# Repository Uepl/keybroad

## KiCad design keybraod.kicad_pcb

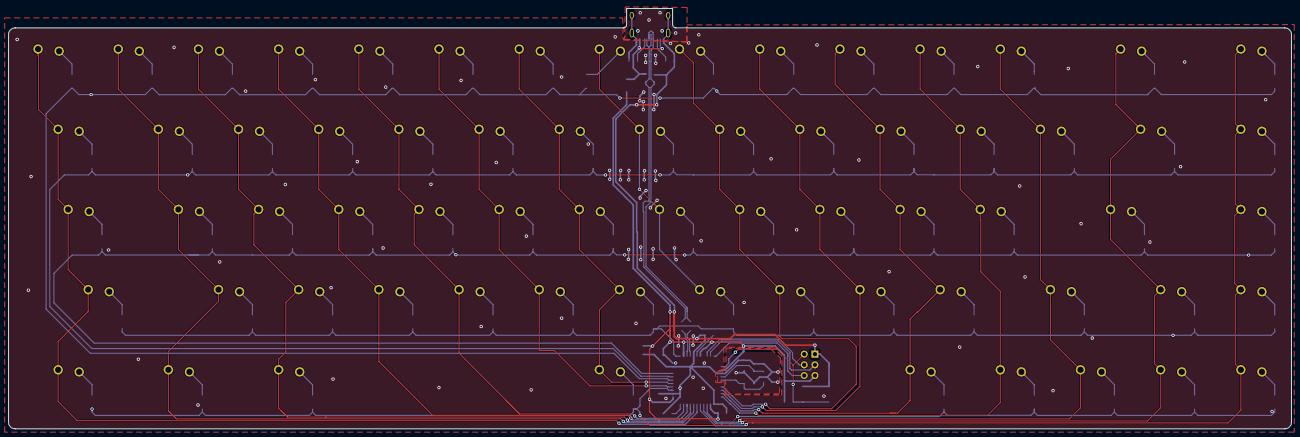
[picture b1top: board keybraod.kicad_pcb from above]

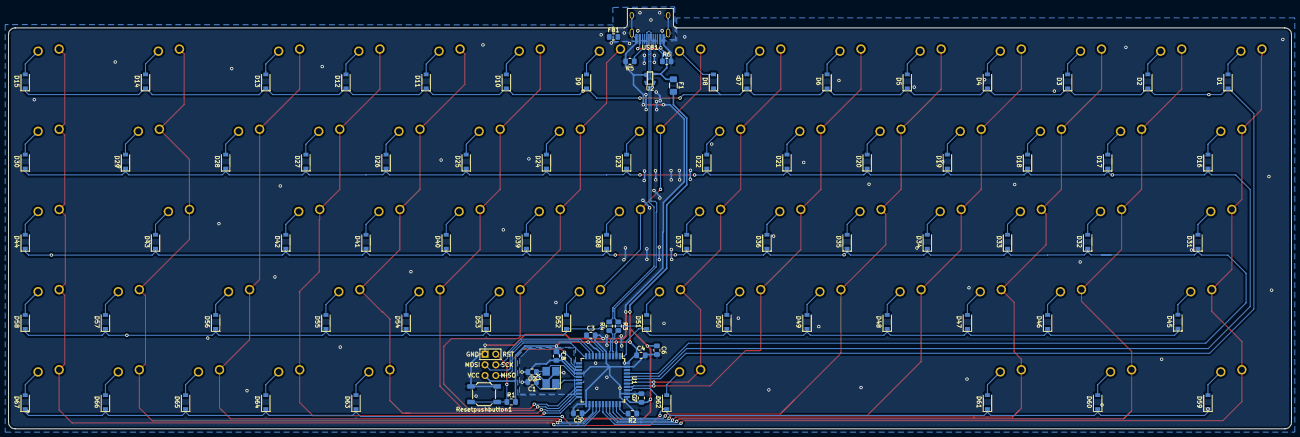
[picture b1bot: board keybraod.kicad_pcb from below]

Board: 2 copper layers, 304.8 x 99.9 mm, 156 parts (156 on the bottom side), 86 nets.

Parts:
C1, C2: 22p; C_0805_2012Metric_Pad1.15x1.40mm_HandSolder
C3: C_Small; C_0805_2012Metric_Pad1.15x1.40mm_HandSolder
C4, C5, C6, C7: 0.1u; C_0805_2012Metric_Pad1.15x1.40mm_HandSolder
C8: 10u; C_0805_2012Metric_Pad1.15x1.40mm_HandSolder
D1, D2, D3, D4, D5, D6, D7, D8, D9, D10, D11, D12, D13, D14, D15, D16, D17, D18, D19, D20, D21, D22, D23, D24, D25, D26, D27, D28, D29, D30, D31, D32, D33, D34, D35, D36, D37, D38, D39, D40, D41, D42, D43, D44, D45, D46, D47, D48, D49, D50, D51, D52, D53, D54, D55, D56, D57, D58, D59, D60, D61, D62, D63, D64, D65, D66, D67: D; D_SOD-123
F1: 500m; Fuse_1206_3216Metric_Pad1.42x1.75mm_HandSolder
FB1: 60@100MHz; L_0805_2012Metric_Pad1.15x1.40mm_HandSolder
J1: AVR-ISP-6; Reset_Pretty-Mask
R1, R2: 10k; R_0805_2012Metric_Pad1.15x1.40mm_HandSolder
R3, R4: 22; R_0805_2012Metric_Pad1.15x1.40mm_HandSolder
R5, R6: 5.1k; R_0805_2012Metric_Pad1.15x1.40mm_HandSolder
Resetpushbutton1: SW_SKQG; SW_SPST_SKQG_WithStem
SW1: GRV; ALPS-1U
SW2: #1; ALPS-1U
SW3: #2; ALPS-1U
SW4: #3; ALPS-1U
SW5: #4; ALPS-1U
SW6: #5; ALPS-1U
SW7: #6; ALPS-1U
SW8: #7; ALPS-1U
SW9: #8; ALPS-1U
SW10: #9; ALPS-1U
SW11: #0; ALPS-1U
SW12: -; ALPS-1U
SW13: =; ALPS-1U
SW14: bs; ALPS-2U
SW15: pgup; ALPS-1U
SW16: tab; ALPS-1.5U
SW17: q; ALPS-1U
SW18: w; ALPS-1U
SW19: e; ALPS-1U
SW20: r; ALPS-1U
SW21: t; ALPS-1U
SW22: y; ALPS-1U
SW23: u; ALPS-1U
SW24: i; ALPS-1U
SW25: o; ALPS-1U
SW26: p; ALPS-1U
SW27: [; ALPS-1U
SW28: ]; ALPS-1U
SW29: \; ALPS-1.5U
SW30: pgdn; ALPS-1U
SW31: caplock; ALPS-1.75U
SW32: a; ALPS-1U
SW33: s; ALPS-1U
SW34: d; ALPS-1U
SW35: f; ALPS-1U
SW36: g; ALPS-1U
SW37: h; ALPS-1U
SW38: j; ALPS-1U
SW39: k; ALPS-1U
SW40: l; ALPS-1U
SW41: ;; ALPS-1U
SW42: '; ALPS-1U
SW43: enter; ALPS-2.25U
SW44: ins; ALPS-1U
SW45: lshift; ALPS-2.25U
SW46: z; ALPS-1U
SW47: x; ALPS-1U
SW48: c; ALPS-1U
SW49: v; ALPS-1U
SW50: b; ALPS-1U
SW51: n; ALPS-1U
SW52: m; ALPS-1U
SW53: ,; ALPS-1U
SW54: .; ALPS-1U
SW55: /; ALPS-1U
SW56: rshift; ALPS-1.75U
SW57: up; ALPS-1U
SW58: del; ALPS-1U
SW59: ctrl; ALPS-1.5U
SW60: lalt; ALPS-1.25U
SW61: cmd; ALPS-1.5U
SW62: spacebar; ALPS-6.5U
SW63: ralt; ALPS-1.25U
SW64: 0; ALPS-1U
SW65: left; ALPS-1U
SW66: down; ALPS-1U
SW67: right; ALPS-1U
U1: ATmega32U4-AU; TQFP-44_10x10mm_P0.8mm
U2: PRTR5V0U2X; SOT143B
USB1: HRO-TYPE-C-31-M-12; HRO-TYPE-C-31-M-12-HandSoldering
X1: XTAL; Crystal_SMD_3225-4Pin_3.2x2.5mm_HandSoldering

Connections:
+5V: C4.1, C5.1, C6.1, C7.1, C8.1, F1.2, J1.2, R1.2, U1.2, U1.7, U1.14, U1.24, U1.34, U1.44
D+: R4.1, U1.4
D-: R3.2, U1.3
DN: R3.1, U2.3, USB1.5, USB1.7
DP: R4.2, U2.2, USB1.6, USB1.8
GND: C1.2, C2.2, C3.2, C4.2, C5.2, C6.2, C7.2, C8.2, J1.6, R2.1, R5.2, R6.2, Resetpushbutton1.2, U1.5, U1.15, U1.23, U1.35, U1.43, U2.1, USB1.1, USB1.12, USB1.13, X1.2, X1.4
MISO: J1.1, U1.11
MOSI: J1.4, U1.10
unnamed: C3.1, U1.6
unnamed: D1.2, SW1.1
unnamed: D2.2, SW2.1
unnamed: D3.2, SW3.1
unnamed: D4.2, SW4.1
unnamed: D5.2, SW5.1
unnamed: D6.2, SW6.1
unnamed: D7.2, SW7.1
unnamed: D8.2, SW8.1
unnamed: D9.2, SW9.1
unnamed: D10.2, SW10.1
unnamed: D11.2, SW11.1
unnamed: D12.2, SW12.1
unnamed: D13.2, SW13.1
unnamed: D14.2, SW14.1
unnamed: D15.2, SW15.1
unnamed: D16.2, SW16.1
unnamed: D17.2, SW17.1
unnamed: D18.2, SW18.1
unnamed: D19.2, SW19.1
unnamed: D20.2, SW20.1
unnamed: D21.2, SW21.1
unnamed: D22.2, SW22.1
unnamed: D23.2, SW23.1
unnamed: D24.2, SW24.1
unnamed: D25.2, SW25.1
unnamed: D26.2, SW26.1
unnamed: D27.2, SW27.1
unnamed: D28.2, SW28.1
unnamed: D29.2, SW29.1
unnamed: D30.2, SW30.1
unnamed: D31.2, SW31.1
unnamed: D32.2, SW32.1
unnamed: D33.2, SW33.1
unnamed: D34.2, SW34.1
unnamed: D35.2, SW35.1
unnamed: D36.2, SW36.1
unnamed: D37.2, SW37.1
unnamed: D38.2, SW38.1
unnamed: D39.2, SW39.1
unnamed: D40.2, SW40.1
unnamed: D41.2, SW41.1
unnamed: D42.2, SW42.1
unnamed: D43.2, SW43.1
unnamed: D44.2, SW44.1
unnamed: D45.2, SW45.1
unnamed: D46.2, SW46.1
unnamed: D47.2, SW47.1
unnamed: D48.2, SW48.1
unnamed: D49.2, SW49.1
unnamed: D50.2, SW50.1
unnamed: D51.2, SW51.1
unnamed: D52.2, SW52.1
unnamed: D53.2, SW53.1
unnamed: D54.2, SW54.1
unnamed: D55.2, SW55.1
unnamed: D56.2, SW56.1
unnamed: D57.2, SW57.1
unnamed: D58.2, SW58.1
unnamed: D59.2, SW59.1
unnamed: D60.2, SW60.1
unnamed: D61.2, SW61.1
unnamed: D62.2, SW62.1
unnamed: D63.2, SW63.1
unnamed: D64.2, SW64.1
unnamed: D65.2, SW65.1
unnamed: D66.2, SW66.1
unnamed: D67.2, SW67.1
unnamed: R2.2, U1.33
unnamed: R5.1, USB1.10
unnamed: R6.1, USB1.4
RESET: J1.5, R1.1, U1.13
SCK: J1.3, U1.9
VCC: F1.1, U2.4, USB1.2, USB1.11
XTAL1: C1.1, U1.17, X1.1
XTAL2: C2.1, U1.16, X1.3
col0: D1.1, D2.1, D3.1, D4.1, D5.1, D6.1, D7.1, D8.1, D9.1, D10.1, D11.1, D12.1, D13.1, D14.1, D15.1, D16.1, D17.1, D18.1, D19.1, D20.1, D21.1, D22.1, D23.1, D24.1, D25.1, D26.1, D27.1, D28.1, D29.1, D30.1, D31.1, D32.1, D33.1, D34.1, D35.1, D36.1, D37.1, D38.1, D39.1, D40.1, D41.1, D42.1, D43.1, D44.1, D45.1, D46.1, D47.1, D48.1, D49.1, D50.1, D51.1, D52.1, D53.1, D54.1, D55.1, D56.1, D57.1, D58.1, D59.1, D60.1, D61.1, D62.1, D63.1, D64.1, D65.1, D66.1, D67.1, SW1.2, SW2.2, SW3.2, SW4.2, SW5.2, SW6.2, SW7.2, SW8.2, SW9.2, SW10.2, SW11.2, SW12.2, SW13.2, SW14.2, SW16.2, SW17.2, SW18.2, SW19.2, SW20.2, SW21.2, SW22.2, SW23.2, SW24.2, SW25.2, SW26.2, SW27.2, SW28.2, SW29.2, SW31.2, SW32.2, SW33.2, SW34.2, SW35.2, SW36.2, SW37.2, SW38.2, SW39.2, SW40.2, SW41.2, SW42.2, SW43.2, SW45.2, SW46.2, SW47.2, SW48.2, SW49.2, SW50.2, SW51.2, SW52.2, SW53.2, SW54.2, SW55.2, SW56.2, SW57.2, SW59.2, SW60.2, SW61.2, SW62.2, SW63.2, SW64.2, SW65.2, SW66.2, U1.1, U1.8, U1.19, U1.20, U1.21, U1.22, U1.25, U1.26, U1.28, U1.29, U1.30, U1.31, U1.32, U1.36, U1.37, U1.38, U1.39, U1.40, U1.41
col14: SW15.2, SW30.2, SW44.2, SW58.2, SW67.2, U1.27

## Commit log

2023-05-30 Add submodules
2023-05-30 part1 complete!
    yes... part1 complete another 3 on the way
2023-05-30 part2 complete
    Yes.. part2 complete, 2 more
2023-05-30 Update fp-info-cache
2023-05-31 part3 complete
    -switch pcb mirror
